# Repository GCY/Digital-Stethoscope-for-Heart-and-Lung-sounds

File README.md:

# Digital-Stethoscope-for-Heart-and-Lung-sounds

## Features
- [x] Headphone(3.5mm) mode for auscultation
- [ ] Heart and Lung Sounds mode switch 
- [ ] Software Filter
  - [ ] Infinite Impulse Response(IIR)
  - [ ] Finite Impulse Response(FIR)  
- [ ] Algorithm
  - [ ] Heart Sound and Lung Sound separation algorithms
- [ ] PC-Host Analysis 
  - [ ] Fast Furious Transform(FFT) amplitude spectrum
  - [ ] Mel Spectrogram
- [ ] SD card operate
  - [ ] Heart and Lung Sounds recoed .wav file to SD card
  - [ ] Replay sample of disease from SD card

## Reference
- Nersisson, R., & Noel, M. M. (2017). Heart sound and lung sound separation algorithms: a review. Journal of medical engineering & technology, 41(1), 13-21.
- Chowdhury, M. E., Khandakar, A., Alzoubi, K., Mansoor, S., M Tahir, A., Reaz, M. B. I., & Al-Emadi, N. (2019). Real-Time Smart-Digital Stethoscope System for Heart Diseases Monitoring. Sensors, 19(12), 2781.
- [How to Bias an Op-Amp](https://ocw.mit.edu/courses/media-arts-and-sciences/mas-836-sensor-technologies-for-interactive-environments-spring-2011/readings/MITMAS_836S11_read02_bias.pdf)
- [Active High Pass Filter](https://www.electronics-tutorials.ws/filter/filter_6.html) 

LICENSE
-------

MIT License

Copyright (c) 2020 Tony Guo https://github.com/GCY

Permission is hereby granted, free of charge, to any person obtaining a copy
of this software and associated documentation files (the "Software"), to deal
in the Software without restriction, including without limitation the rights
to use, copy, modify, merge, publish, distribute, sublicense, and/or sell
copies of the Software, and to permit persons to whom the Software is
furnished to do so, subject to the following conditions:

The above copyright notice and this permission notice shall be included in all
copies or substantial portions of the Software.

THE SOFTWARE IS PROVIDED "AS IS", WITHOUT WARRANTY OF ANY KIND, EXPRESS OR
IMPLIED, INCLUDING BUT NOT LIMITED TO THE WARRANTIES OF MERCHANTABILITY,
FITNESS FOR A PARTICULAR PURPOSE AND NONINFRINGEMENT. IN NO EVENT SHALL THE
AUTHORS OR COPYRIGHT HOLDERS BE LIABLE FOR ANY CLAIM, DAMAGES OR OTHER
LIABILITY, WHETHER IN AN ACTION OF CONTRACT, TORT OR OTHERWISE, ARISING FROM,
OUT OF OR IN CONNECTION WITH THE SOFTWARE OR THE USE OR OTHER DEALINGS IN THE
SOFTWARE.

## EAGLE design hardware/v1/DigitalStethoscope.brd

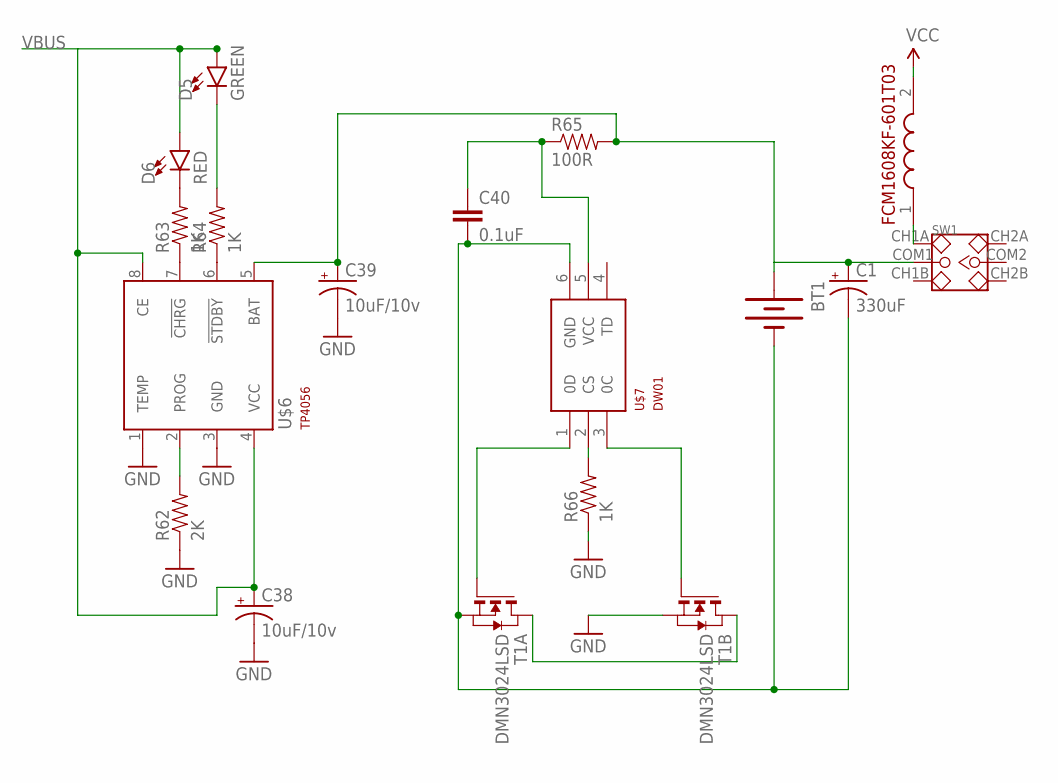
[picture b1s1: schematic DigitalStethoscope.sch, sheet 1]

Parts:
BT1: BATTERYLIPO-TABS; LIPO-110-TABS
C1: 330uF; E3,5-8
C38, C39: 10uF/10v; EIA3216-KIT
C40: 0.1uF; 0603-CAP
D5: GREEN; LED-0603
D6: RED; LED-0603
R62: 2K; 0603-RES
R63, R64, R66: 1K; 0603-RES
R65: 100R; 0603-RES
SW1: SMD-TOGGLE-SWITCH-2CH(2X3P-7X3.5MM); SW6-2.54-SMD-7.0X3.5X1.5MM
T1: DMN3024LSD; TSSOP-8
U$4: FCM1608KF-601T03
U$6: TP4056; SOT23-8
U$7: DW01; SOT23-6

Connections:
GND: C38.C (-), C39.C (-), R62.1, R66.1, T1.6 (S), T1.7 (S), U$6.1 (TEMP), U$6.3 (GND); also elsewhere on the board
unnamed: BT1.+, C1.+, C39.A (+), R65.2, SW1.COM1, U$6.5 (BAT)
unnamed: R62.2, U$6.2 (PROG)
unnamed: R63.1, U$6.7 (!CHRG)
unnamed: R64.1, U$6.6 (!STDBY)
unnamed: D6.C, R63.2
unnamed: D5.C, R64.2
unnamed: C40.1, R65.1, U$7.5 (VCC)
unnamed: BT1.-, C1.-, C40.2, T1.2 (S), T1.3 (S), U$7.6 (GND)
unnamed: T1.4 (G), U$7.1 (0D)
unnamed: R66.2, U$7.2 (CS)
unnamed: T1.1 (D), T1.8 (D)
unnamed: T1.5 (G), U$7.3 (0C)
unnamed: SW1.CH1A, U$4.1 (1.IN)
VBUS: C38.A (+), D5.A, D6.A, U$6.4 (VCC), U$6.8 (CE); also elsewhere on the board
VCC: U$4.2 (2.OUT); also elsewhere on the board

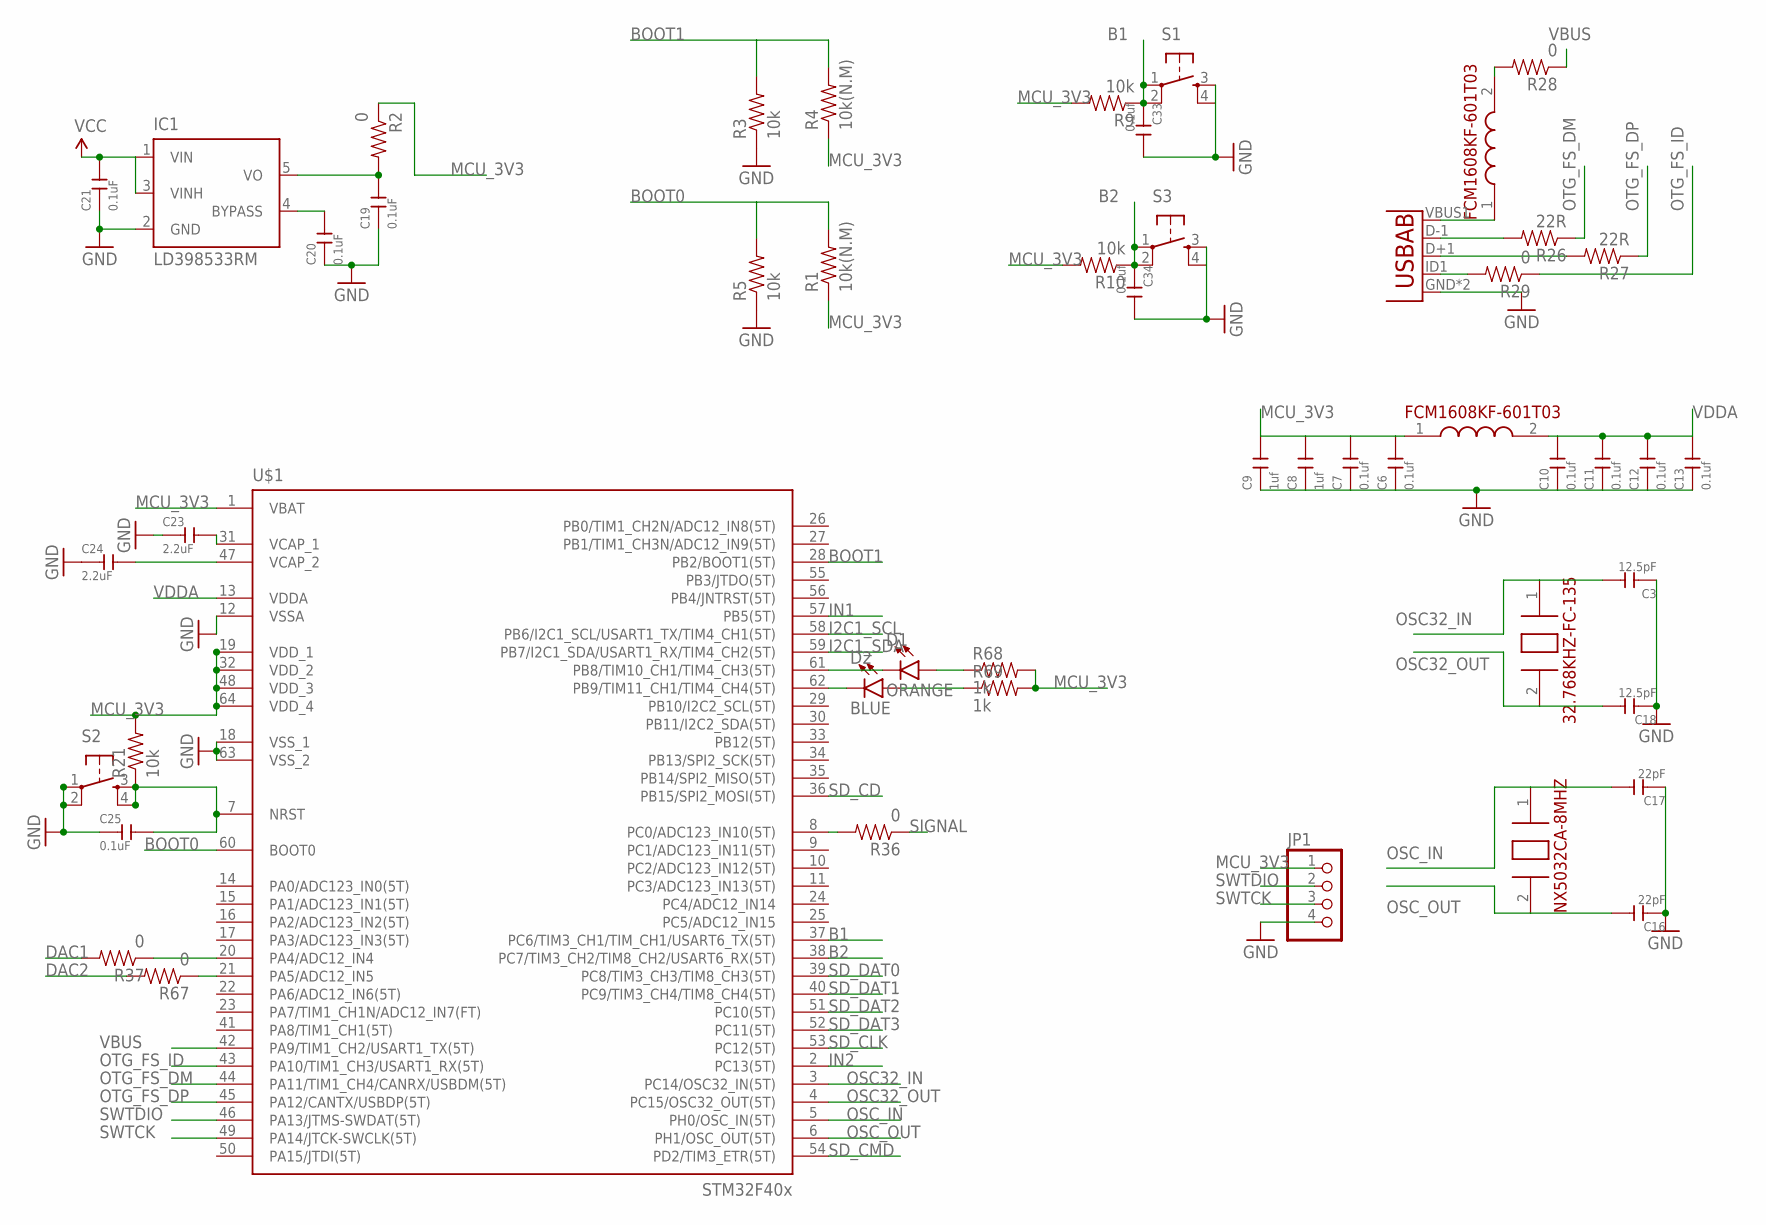
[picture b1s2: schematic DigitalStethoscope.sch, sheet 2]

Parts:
C3, C18: 12.5pF; C0603
C6, C7, C10, C11, C12, C13, C33, C34: 0.1uf; C0603
C8, C9: 1uf; C0603
C16, C17: 22pF; C0603
C19, C20, C21, C25: 0.1uF; C0603
C23, C24: 2.2uF; C0603
D1: ORANGE; LED-0603
D2: BLUE; LED-0603
IC1: LD398533RM; SOT23-5L
JP1: PINHD-1X4; 1X04
R1, R4: 10k(N.M); 0603
R2, R28, R29, R36, R37, R67: 0; 0603-RES
R3, R5, R9, R10: 10k; 0603
R21: 10k; 0603-RES
R26, R27: 22R; 0603-RES
R68, R69: 1k; 0603-RES
S1, S2, S3: TAC_SWITCHSMD; TACTILE_SWITCH_SMD
U4: USB""; USB-MICRO-SMD
U$1: STM32F405R; TQFP64
U$2: 32.768KHZ-FC-135
U$3, U$5: FCM1608KF-601T03
U$8: NX5032CA-8MHZ

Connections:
B1: C33.1, R9.1, S1.1, S1.2, U$1.37 (PC6/TIM3_CH1/TIM_CH1/USART6_TX(5T))
B2: C34.1, R10.1, S3.1, S3.2, U$1.38 (PC7/TIM3_CH2/TIM8_CH2/USART6_RX(5T))
BOOT0: R1.2, R5.2, U$1.60 (BOOT0)
BOOT1: R3.2, R4.2, U$1.28 (PB2/BOOT1(5T))
DAC1: R37.2; also elsewhere on the board
DAC2: R67.2; also elsewhere on the board
GND: C3.1, C6.1, C7.1, C8.1, C9.1, C10.1, C11.1, C12.1, C13.1, C16.1, C17.1, C18.1, C19.1, C20.1, C21.1, C23.1, C24.1, C25.1, C33.2, C34.2, IC1.2 (GND), JP1.4, R3.1, R5.1, S1.3, S1.4, S2.1, S2.2, S3.3, S3.4, U4.GND, U4.GND1 (GND), U$1.12 (VSSA), U$1.18 (VSS_1), U$1.63 (VSS_2); also elsewhere on the board
I2C1_SCL: U$1.58 (PB6/I2C1_SCL/USART1_TX/TIM4_CH1(5T)); also elsewhere on the board
I2C1_SDA: U$1.59 (PB7/I2C1_SDA/USART1_RX/TIM4_CH2(5T)); also elsewhere on the board
IN1: U$1.57 (PB5(5T)); also elsewhere on the board
IN2: U$1.2 (PC13(5T)); also elsewhere on the board
MCU_3V3: C6.2, C7.2, C8.2, C9.2, JP1.1, R1.1, R2.1, R4.1, R9.2, R10.2, R21.2, R68.2, R69.2, U$1.1 (VBAT), U$1.19 (VDD_1), U$1.32 (VDD_2), U$1.48 (VDD_3), U$1.64 (VDD_4), U$3.1 (1.IN); also elsewhere on the board
unnamed: C20.2, IC1.4 (BYPASS)
unnamed: R36.2, U$1.8 (PC0/ADC123_IN10(5T))
unnamed: R26.2, U4.D-1 (D-)
unnamed: C23.2, U$1.31 (VCAP_1)
unnamed: C24.2, U$1.47 (VCAP_2)
unnamed: R37.1, U$1.20 (PA4/ADC12_IN4)
unnamed: C25.2, R21.1, S2.3, S2.4, U$1.7 (NRST)
unnamed: C19.2, IC1.5 (VO), R2.2
unnamed: R27.2, U4.D+1 (D+)
unnamed: U4.VBUS1 (VBUS), U$5.1 (1.IN)
unnamed: R29.2, U4.ID1 (USBID)
unnamed: R28.2, U$5.2 (2.OUT)
unnamed: R67.1, U$1.21 (PA5/ADC12_IN5)
unnamed: D2.C, U$1.62 (PB9/TIM11_CH1/TIM4_CH4(5T))
unnamed: D1.C, U$1.61 (PB8/TIM10_CH1/TIM4_CH3(5T))
unnamed: D1.A, R68.1
unnamed: D2.A, R69.1
OSC32_IN: C3.2, U$1.3 (PC14/OSC32_IN(5T)), U$2.1 (1.XIN)
OSC32_OUT: C18.2, U$1.4 (PC15/OSC32_OUT(5T)), U$2.2 (2.XIN)
OSC_IN: C17.2, U$1.5 (PH0/OSC_IN(5T)), U$8.1 (1.XIN)
OSC_OUT: C16.2, U$1.6 (PH1/OSC_OUT(5T)), U$8.2 (2.XOUT)
OTG_FS_DM: R26.1, U$1.44 (PA11/TIM1_CH4/CANRX/USBDM(5T))
OTG_FS_DP: R27.1, U$1.45 (PA12/CANTX/USBDP(5T))
OTG_FS_ID: R29.1, U$1.43 (PA10/TIM1_CH3/USART1_RX(5T))
SD_CD: U$1.36 (PB15/SPI2_MOSI(5T)); also elsewhere on the board
SD_CLK: U$1.53 (PC12(5T)); also elsewhere on the board
SD_CMD: U$1.54 (PD2/TIM3_ETR(5T)); also elsewhere on the board
SD_DAT0: U$1.39 (PC8/TIM3_CH3/TIM8_CH3(5T)); also elsewhere on the board
SD_DAT1: U$1.40 (PC9/TIM3_CH4/TIM8_CH4(5T)); also elsewhere on the board
SD_DAT2: U$1.51 (PC10(5T)); also elsewhere on the board
SD_DAT3: U$1.52 (PC11(5T)); also elsewhere on the board
SIGNAL: R36.1; also elsewhere on the board
SWTCK: JP1.3, U$1.49 (PA14/JTCK-SWCLK(5T))
SWTDIO: JP1.2, U$1.46 (PA13/JTMS-SWDAT(5T))
VBUS: R28.1, U$1.42 (PA9/TIM1_CH2/USART1_TX(5T)); also elsewhere on the board
VCC: C21.2, IC1.1 (VIN), IC1.3 (VINH); also elsewhere on the board
VDDA: C10.2, C11.2, C12.2, C13.2, U$1.13 (VDDA), U$3.2 (2.OUT)

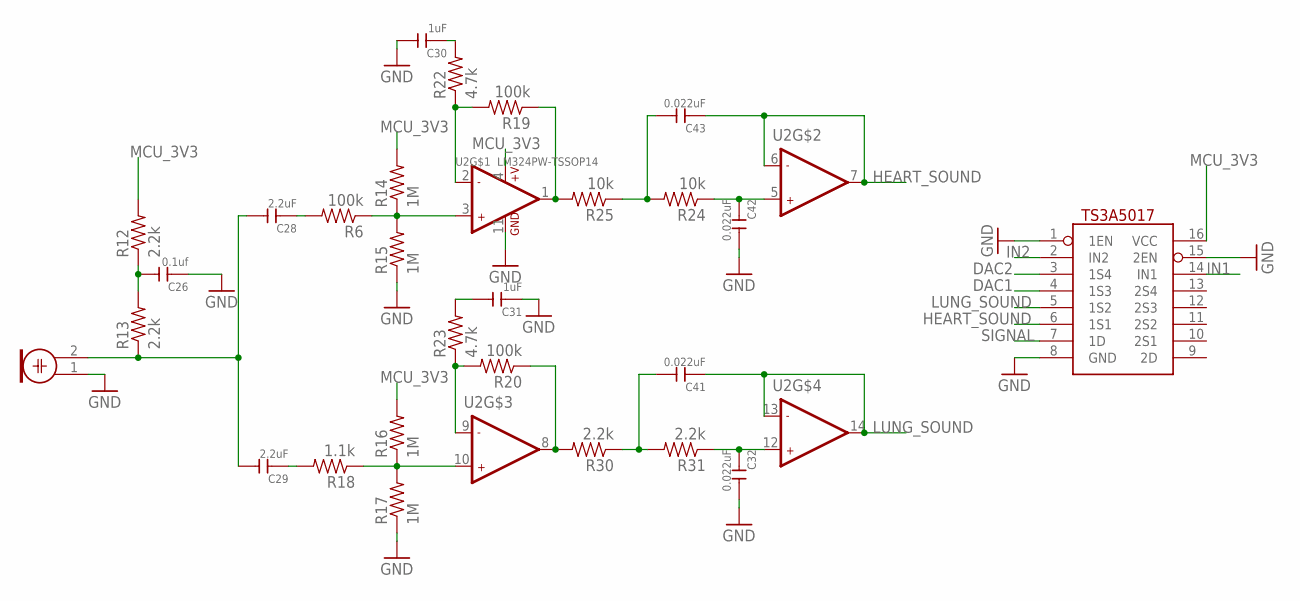
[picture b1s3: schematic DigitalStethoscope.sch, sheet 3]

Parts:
ASW: MUX-TS3A5017; SO16
C26: 0.1uf; C0603
C28, C29: 2.2uF; C0603
C30, C31: 1uF; C0603
C32, C41, C42, C43: 0.022uF; C0603
M1: ELECTRET_MICROPHON-F6035AP; F6035AP
R6, R19, R20: 100k; 0603-RES
R12, R13, R30, R31: 2.2k; 0603-RES
R14, R15, R16, R17: 1M; 0603-RES
R18: 1.1k; 0603-RES
R22, R23: 4.7k; 0603-RES
R24, R25: 10k; 0603-RES
U2: LM324PW-TSSOP14; TSSOP14-0.65-5X4.4MM

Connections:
DAC1: ASW.4 (1S3); also elsewhere on the board
DAC2: ASW.3 (1S4); also elsewhere on the board
GND: ASW.1 (1EN), ASW.8 (GND), ASW.15 (2EN), C26.1, C30.2, C31.1, C32.2, C42.2, M1.1, R15.1, R17.1, U2.11 (GND); also elsewhere on the board
HEART_SOUND: ASW.6 (1S1), C43.1, U2.6 (-IN2), U2.7 (OUT2)
IN1: ASW.14 (IN1); also elsewhere on the board
IN2: ASW.2 (IN2); also elsewhere on the board
LUNG_SOUND: ASW.5 (1S2), C41.1, U2.13 (-IN2), U2.14 (OUT2)
MCU_3V3: ASW.16 (VCC), R12.2, R14.2, R16.2, U2.4 (+V); also elsewhere on the board
unnamed: C26.2, R12.1, R13.2
unnamed: C28.2, C29.2, M1.2, R13.1
unnamed: R6.1, R14.1, R15.2, U2.3 (+IN1)
unnamed: R16.1, R17.2, R18.1, U2.10 (+IN2)
unnamed: C29.1, R18.2
unnamed: C28.1, R6.2
unnamed: R19.2, R22.1, U2.2 (-IN1)
unnamed: R19.1, R25.2, U2.1 (OUT1)
unnamed: C30.1, R22.2
unnamed: R20.2, R23.1, U2.9 (-IN2)
unnamed: R20.1, R30.2, U2.8 (OUT2)
unnamed: C31.2, R23.2
unnamed: C43.2, R24.2, R25.1
unnamed: C42.1, R24.1, U2.5 (+IN2)
unnamed: C41.2, R30.1, R31.2
unnamed: C32.1, R31.1, U2.12 (+IN2)
SIGNAL: ASW.7 (1D); also elsewhere on the board

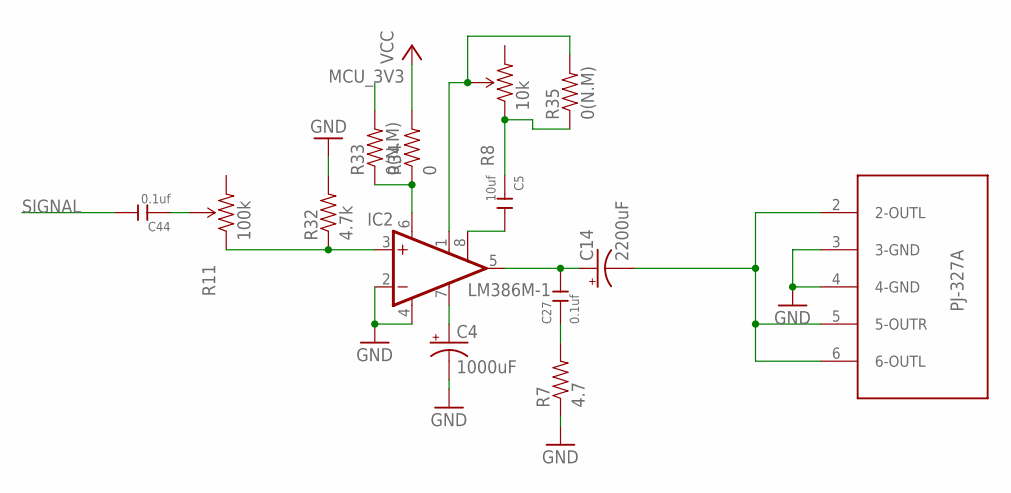
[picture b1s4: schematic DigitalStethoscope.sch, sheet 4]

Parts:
C4: 1000uF; E3,5-8
C5: 10uf; C0603
C14: 2200uF; E3,5-8
C27, C44: 0.1uf; C0603
IC2: LM386M-1; SO08
R7: 4.7; 0603-RES
R8: 10k; TRIMPOT_TC33
R11: 100k; TRIMPOT_TC33
R32: 4.7k; 0603-RES
R33, R35: 0(N.M); 0603-RES
R34: 0; 0603-RES
U$9: PJ-327A

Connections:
GND: C4.-, IC2.2 (-IN), IC2.4 (GND), R7.1, R32.2, U$9.3 (3-GND), U$9.4 (4-GND); also elsewhere on the board
MCU_3V3: R33.2; also elsewhere on the board
unnamed: IC2.3 (+IN), R11.1 (CCW), R32.1
unnamed: C44.1, R11.2 (WIPER)
unnamed: C4.+, IC2.7 (BYPASS)
unnamed: C14.+, C27.2, IC2.5 (OUT)
unnamed: C27.1, R7.2
unnamed: C5.2, IC2.8 (GAIN)
unnamed: C5.1, R8.1 (CCW), R35.1
unnamed: IC2.1 (GAIN), R8.2 (WIPER), R35.2
unnamed: C14.-, U$9.2 (2-OUTL), U$9.5 (5-OUTR), U$9.6 (6-OUTL)
unnamed: IC2.6 (VS), R33.1, R34.1
SIGNAL: C44.2; also elsewhere on the board
VCC: R34.2; also elsewhere on the board

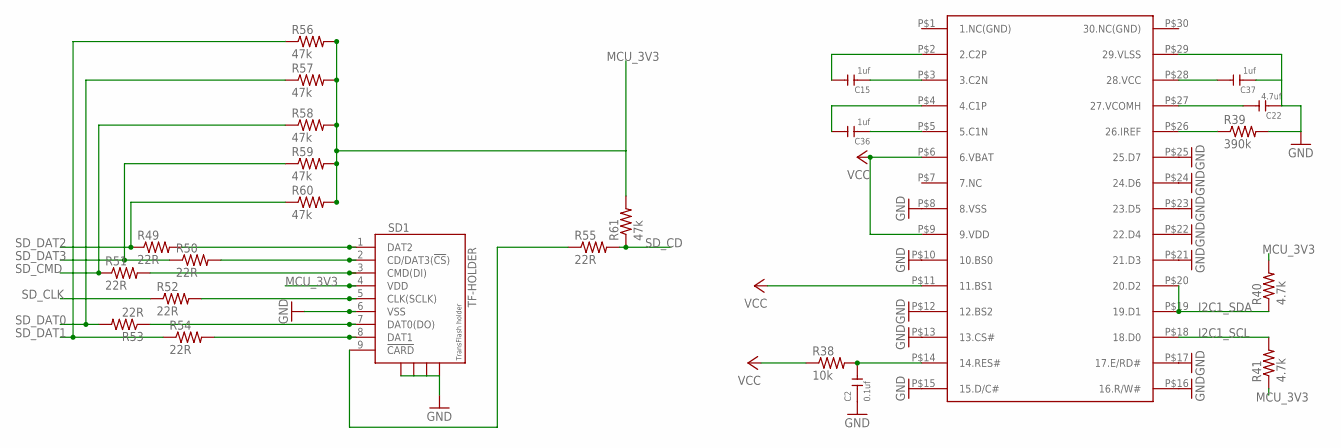
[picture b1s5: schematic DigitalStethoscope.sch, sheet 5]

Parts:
C2: 0.1uf; C0603
C15, C36, C37: 1uf; C0603
C22: 4.7uf; C0603
R38: 10k; 0603
R39: 390k; 0603
R40, R41: 4.7k; 0603
R49, R50, R51, R52, R53, R54, R55: 22R; 0603-RES
R56, R57, R58, R59, R60, R61: 47k; 0603-RES
SD1: TF-HOLDER; TF-PULL
U$18: ER-OLED0.96

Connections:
GND: C2.1, C22.1, C37.1, R39.2, SD1.6 (VSS), SD1.S1, SD1.S2, SD1.S3, SD1.S4, U$18.P$8 (8.VSS), U$18.P$10 (10.BS0), U$18.P$12 (12.BS2), U$18.P$13 (13.CS#), U$18.P$15 (15.D/C#), U$18.P$16 (16.R/W#), U$18.P$17 (17.E/RD#), U$18.P$21 (21.D3), U$18.P$22 (22.D4), U$18.P$23 (23.D5), U$18.P$24 (24.D6), U$18.P$25 (25.D7), U$18.P$29 (29.VLSS); also elsewhere on the board
I2C1_SCL: R41.2, U$18.P$18 (18.D0); also elsewhere on the board
I2C1_SDA: R40.1, U$18.P$19 (19.D1), U$18.P$20 (20.D2); also elsewhere on the board
MCU_3V3: R40.2, R41.1, R56.2, R57.2, R58.2, R59.2, R60.2, R61.2, SD1.4 (VDD); also elsewhere on the board
unnamed: R49.2, SD1.1 (DAT2)
unnamed: C2.2, R38.2, U$18.P$14 (14.RES#)
unnamed: C15.1, U$18.P$3 (3.C2N)
unnamed: C36.1, U$18.P$5 (5.C1N)
unnamed: C15.2, U$18.P$2 (2.C2P)
unnamed: C36.2, U$18.P$4 (4.C1P)
unnamed: R39.1, U$18.P$26 (26.IREF)
unnamed: C22.2, U$18.P$27 (27.VCOMH)
unnamed: C37.2, U$18.P$28 (28.VCC)
unnamed: R50.2, SD1.2 (CD/DAT3(!CS!))
unnamed: R51.2, SD1.3 (CMD(DI))
unnamed: R52.2, SD1.5 (CLK(SCLK))
unnamed: R53.1, SD1.7 (DAT0(DO))
unnamed: R54.2, SD1.8 (DAT1)
unnamed: R55.1, SD1.9 (!CARD)
SD_CD: R55.2, R61.1; also elsewhere on the board
SD_CLK: R52.1; also elsewhere on the board
SD_CMD: R51.1, R58.1; also elsewhere on the board
SD_DAT0: R53.2, R57.1; also elsewhere on the board
SD_DAT1: R54.1, R56.1; also elsewhere on the board
SD_DAT2: R49.1, R60.1; also elsewhere on the board
SD_DAT3: R50.1, R59.1; also elsewhere on the board
VCC: R38.1, U$18.P$6 (6.VBAT), U$18.P$9 (9.VDD), U$18.P$11 (11.BS1); also elsewhere on the board

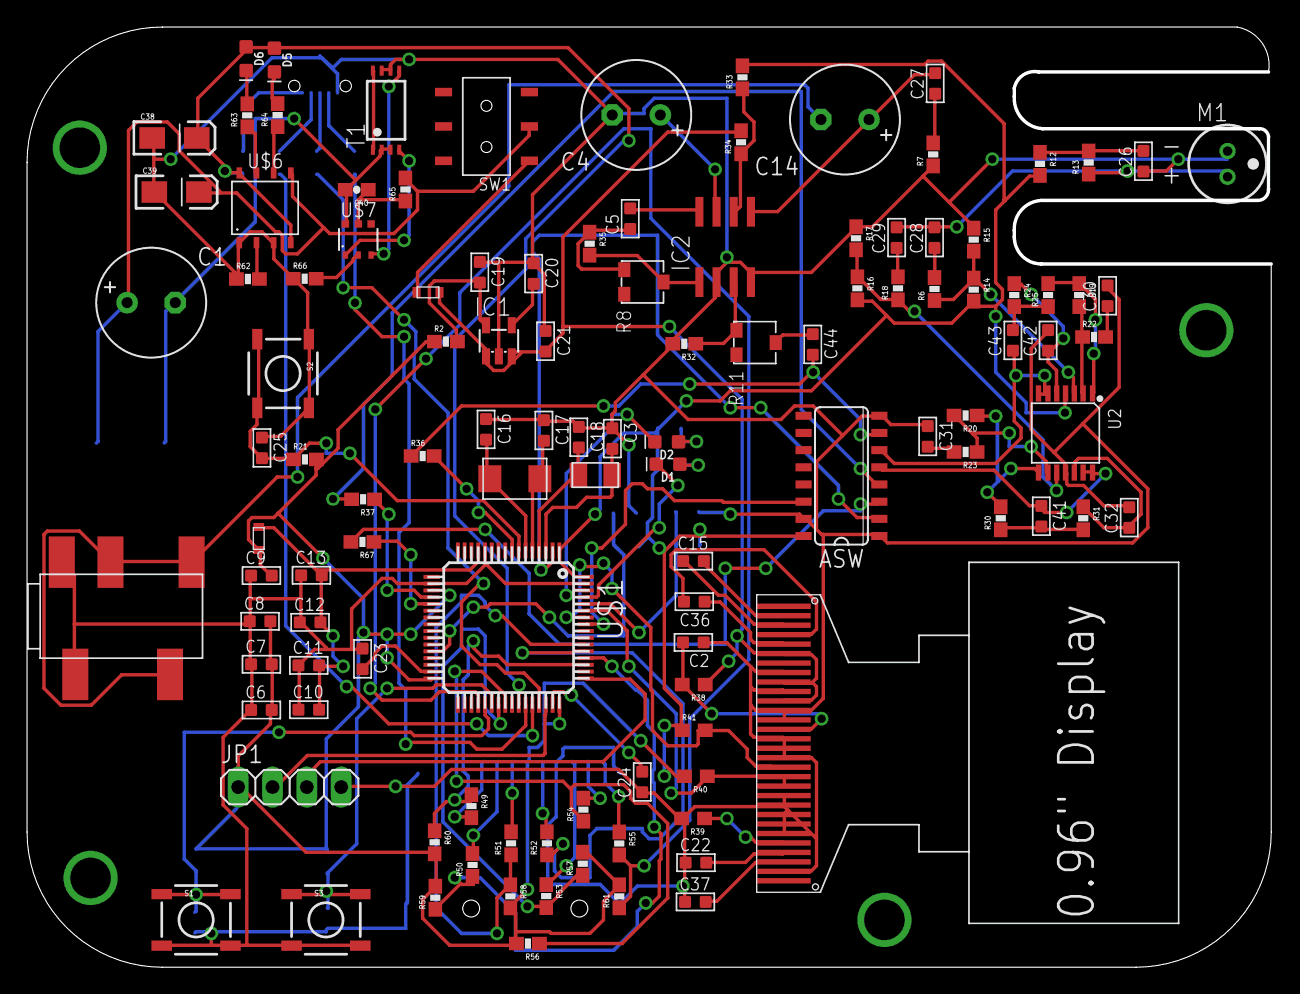
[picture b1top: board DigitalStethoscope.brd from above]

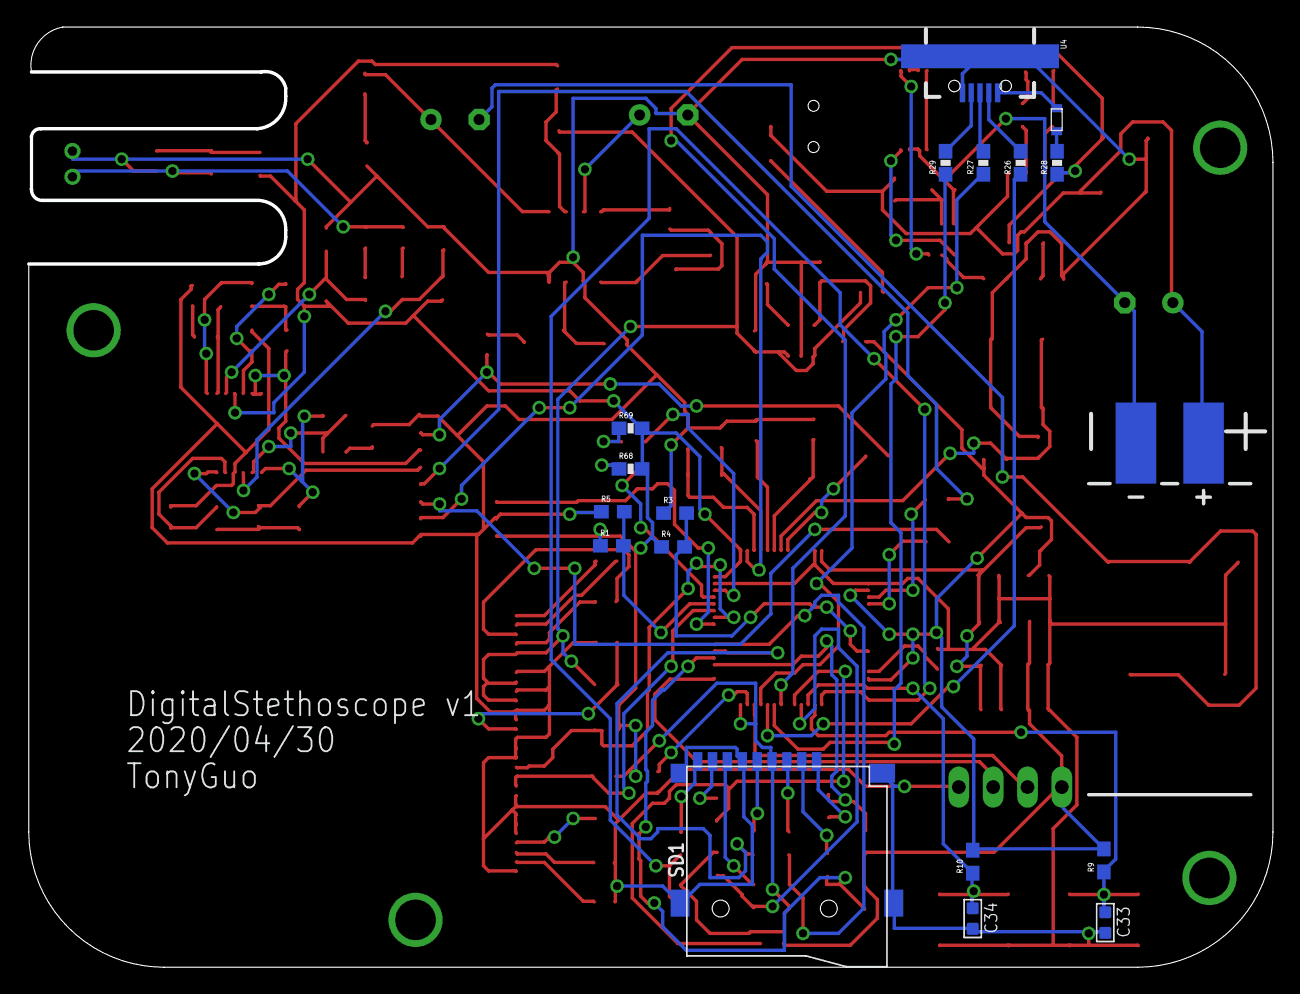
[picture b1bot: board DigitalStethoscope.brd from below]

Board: 2 copper layers, 92.0 x 69.5 mm, 133 parts (18 on the bottom side), 105 nets.

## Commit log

2020-04-28 prototype
2020-05-03 v1 PCB Layout
2020-05-18 V1 PCB
2020-05-25 Analog Front End
2020-08-26 USB Audio Class dataIn from ADC

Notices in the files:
parts and their libraries:
SparkFun-Capacitors: Licensing: CC v3.0 Share-Alike You are welcome to use this library for commercial purposes.
SparkFun-Retired: Licensing: Creative Commons ShareAlike 4.0 International - https://creativecommons.org/licenses/by-sa/4.0
